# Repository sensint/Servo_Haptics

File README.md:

<div id="top"></div>

<!-- PROJECT SHIELDS -->
<!--
*** I'm using markdown "reference style" links for readability.
*** Reference links are enclosed in brackets [ ] instead of parentheses ( ).
*** See the bottom of this document for the declaration of the reference variables
*** for contributors-url, forks-url, etc. This is an optional, concise syntax you may use.
*** https://www.markdownguide.org/basic-syntax/#reference-style-links
-->
[![Contributors][contributors-shield]][contributors-url]
[![Forks][forks-shield]][forks-url]
[![Stargazers][stars-shield]][stars-url]
[![Issues][issues-shield]][issues-url]
[![MIT License][license-shield]][license-url]

<!-- PROJECT LOGO -->
<br />
<div align="center">

<h3 align="center">Haptic Servos - Motion Coupled Vibrations</h3>

  <p align="center">
    Self-Contained Vibrotactile Rendering System for Creating or Augmenting Material Experiences
    <br />
    <b>We'd love to get your feedback and get in touch with you: https://forms.gle/Dh4iDR7DPDSnXZQTA</b>
    <br />
    <br />
    <a href="https://github.com/sensint/Servo_Haptics/issues">Report Bug</a>
    ·
    <a href="https://github.com/sensint/Servo_Haptics/issues">Request Feature</a>
  </p>
</div>

## About The Project

![Banner images][banner-image]

<!--Add a summary of the project.-->

<p align="right">(<a href="#top">back to top</a>)</p>

### Built With

* [Teensyduino](https://www.pjrc.com/teensy/teensyduino.html)
* [PlatformIO](https://platformio.org/)

<p align="right">(<a href="#top">back to top</a>)</p>

## Getting Started

Download the code from the GitHub website or clone repo using your favorite git-client software or with the following command:

   ```sh
   git clone https://github.com/sensint/Servo_Haptics.git
   ```

### Firmware

We provide the firmware for two build systems - Teensyduino (based on Arduino IDE) and PlatformIO.

The firmware was tested with the following microcontrollers:

- Teensy 3.5
- Teensy 4.1

#### Teensyduino

The easiest way to get up and running with the firmware is Teensyduino.

##### Prerequisites

Download and install the [Teensyduino](https://www.pjrc.com/teensy/td_download.html) software for your operating system. All needed libraries are included in the basic installation.

##### Build and Upload

1. Open the `HapticServo.ino`
    1. navigate in your file manager (Win: Explorer, macOS: Finder) to the repository's folder `firmware/Teensyduino/MotionCoupledVibrations` and then double-click the `ino` file
    2. use the Teensyduino menu (`File -> Open`) or the keyboard shortcut (Win: `Ctrl+O`, macOS: `Cmd+O`) and navigate to the repository's folder `firmware/Teensyduino/MotionCoupledVibrations` and then select the `ino` file
2. connect the Teensy with your computer via USB
3. configure the Teensyduino
    1. select the correct board (Teensy version) from `Tools -> Board -> Teensydunio`
    2. select the correct serial port from `Tools -> Port`
4. click the upload button (arrow) in the Teensyduino IDE

<p align="right">(<a href="#top">back to top</a>)</p>

##### Control

The Haptic Servo is designed to be compatible with servo hardware and software. Using servo-commands you can fine-tune the tactile experience. You can find an example of how to do this in 'ServoControl.ino'

#### PlatformIO

##### Prerequisites

##### Build and Upload

<p align="right">(<a href="#top">back to top</a>)</p>

### Hardware

This project is based on the Teensy microcontroller and the [PT8211 Audio Kit](https://www.pjrc.com/store/pt8211_kit.html).

<p align="right">(<a href="#top">back to top</a>)</p>

## Usage

<!--Use this space to show useful examples of how a project can be used. Additional screenshots, code examples and demos work well in this space. You may also link to more resources.-->

<p align="right">(<a href="#top">back to top</a>)</p>

## Roadmap

See the [open issues](https://github.com/sensint/Servo_Haptics/issues) for a full list of proposed features (and known issues).

### Firmware

- [ ] ...

### Hardware

- [ ] ...

<p align="right">(<a href="#top">back to top</a>)</p>

## Contributing

Contributions are what make the open source community such an amazing place to learn, inspire, and create. Any contributions you make are **greatly appreciated**.

If you have a suggestion that would make this better, please fork the repo and create a pull request. You can also simply open an issue with the tag "enhancement".
Don't forget to give the project a star! Thanks again!

1. Fork the Project
2. Create your Feature Branch (`git checkout -b feature/AmazingFeature`)
3. Commit your Changes (`git commit -m 'Add some AmazingFeature'`)
4. Push to the Branch (`git push origin feature/AmazingFeature`)
5. Open a Pull Request

<p align="right">(<a href="#top">back to top</a>)</p>

## License

Distributed under the MIT License. See `LICENSE.txt` for more information.

<p align="right">(<a href="#top">back to top</a>)</p>

## Contact

Sensorimotor Interaction Group - [website](https://sensint.mpi-inf.mpg.de/) - [@sensintgroup](https://twitter.com/sensintgroup)

Project Link: [https://github.com/sensint/Servo_Haptics](https://github.com/sensint/Servo_Haptics)

<p align="right">(<a href="#top">back to top</a>)</p>

## Acknowledgments

* Othneil Drew for [Best-README-Template](https://github.com/othneildrew/Best-README-Template)

<p align="right">(<a href="#top">back to top</a>)</p>

<!-- MARKDOWN LINKS & IMAGES -->
<!-- https://www.markdownguide.org/basic-syntax/#reference-style-links -->
[contributors-shield]: https://img.shields.io/github/contributors/sensint/Servo_Haptics.svg?style=for-the-badge
[contributors-url]: https://github.com/sensint/Servo_Haptics/graphs/contributors
[forks-shield]: https://img.shields.io/github/forks/sensint/Servo_Haptics.svg?style=for-the-badge
[forks-url]: https://github.com/sensint/Servo_Haptics/network/members
[stars-shield]: https://img.shields.io/github/stars/sensint/Servo_Haptics.svg?style=for-the-badge
[stars-url]: https://github.com/sensint/Servo_Haptics/stargazers
[issues-shield]: https://img.shields.io/github/issues/sensint/Servo_Haptics.svg?style=for-the-badge
[issues-url]: https://github.com/sensint/Servo_Haptics/issues
[license-shield]: https://img.shields.io/github/license/sensint/Servo_Haptics.svg?style=for-the-badge
[license-url]: https://github.com/sensint/Servo_Haptics/blob/master/LICENSE
[banner-image]: assets/img/banner_temp.PNG

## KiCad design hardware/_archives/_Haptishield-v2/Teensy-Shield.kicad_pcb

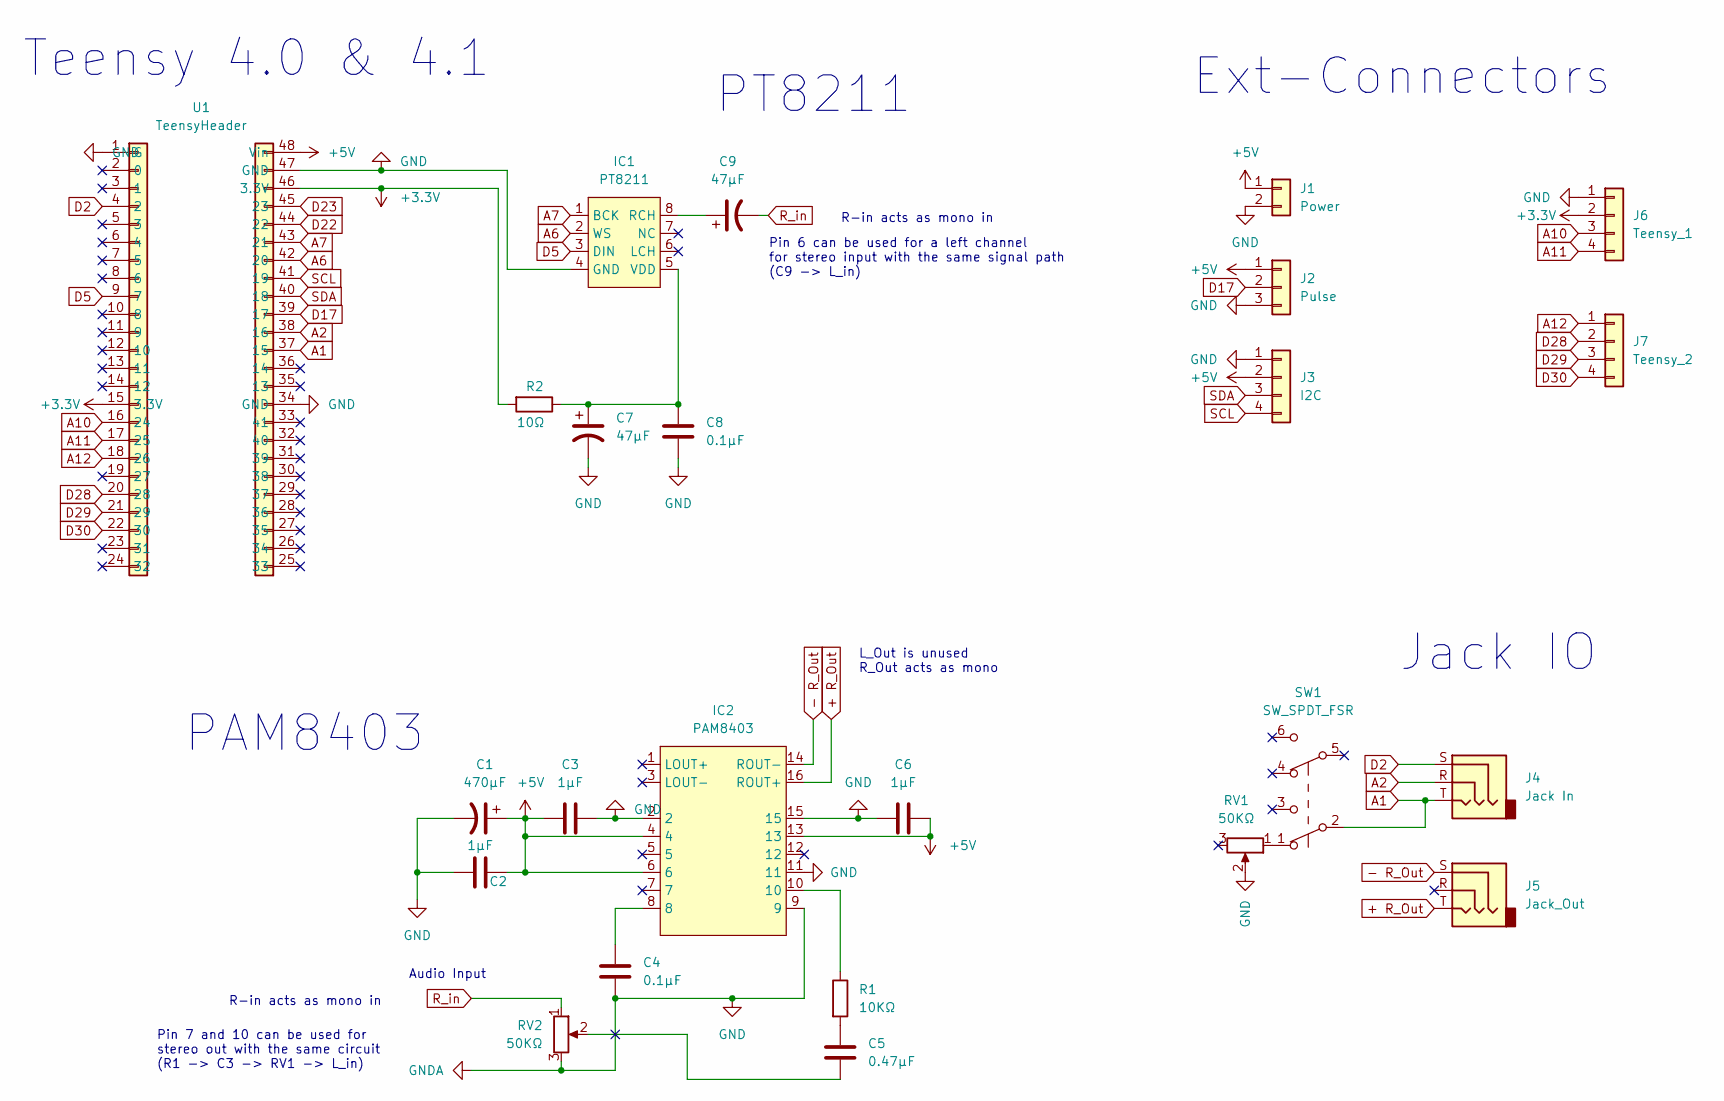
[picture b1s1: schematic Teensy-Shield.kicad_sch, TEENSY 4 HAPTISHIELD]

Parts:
C1: 470µF; CP_Radial_D5.0mm_P2.00mm
C2, C3, C6: 1µF; C_0805_2012Metric_Pad1.18x1.45mm_HandSolder
C4, C8: 0.1µF; C_0805_2012Metric_Pad1.18x1.45mm_HandSolder
C5: 0.47µF; C_0805_2012Metric_Pad1.18x1.45mm_HandSolder
C7, C9: 47µF; CP_Radial_D4.0mm_P1.50mm
IC1: PT8211; SOP-8_3.9x4.9mm_P1.27mm
IC2: PAM8403; SOIC-16_3.9x9.9mm_P1.27mm
J1: Power; PinHeader_1x02_P2.54mm_Vertical
J2: Pulse; PinHeader_1x03_P2.54mm_Vertical
J3: I2C; PinHeader_1x04_P2.54mm_Vertical
J4: Jack In; Jack_3.5mm_CUI_SJ1-3535NG_Horizontal_CircularHoles
J5: Jack_Out; Jack_3.5mm_CUI_SJ1-3535NG_Horizontal_CircularHoles
J6: Teensy_1; PinHeader_1x04_P2.54mm_Vertical
J7: Teensy_2; PinHeader_1x04_P2.54mm_Vertical
R1: 10KΩ; R_0805_2012Metric_Pad1.20x1.40mm_HandSolder
R2: 10Ω; R_0805_2012Metric_Pad1.20x1.40mm_HandSolder
RV1, RV2: 50KΩ; TRIM_3362P-1-503TLF
SW1: SW_SPDT_FSR; SW_CuK_JS202011CQN_DPDT_Straight
U1: TeensyHeader; Teensy41

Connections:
+3V3: J6.2, R2.2, U1.15 (3.3V), U1.46 (3.3V)
+5V: C1.1, C2.2, C3.1, C6.2, IC2.4, IC2.6, IC2.13, J1.1, J2.1, J3.2, U1.48 (Vin)
+ R_Out: IC2.16 (ROUT+), J5.T
- R_Out: IC2.14 (ROUT-), J5.S
A1: J4.T, SW1.2 (B), U1.37 (15)
A2: J4.R, U1.38 (16)
A6: IC1.2 (WS), U1.42 (20)
A7: IC1.1 (BCK), U1.43 (21)
A10: J6.3, U1.16 (24)
A11: J6.4, U1.17 (25)
A12: J7.1, U1.18 (26)
D2: J4.S, U1.4 (2)
D5: IC1.3 (DIN), U1.9 (7)
D17: J2.2, U1.39 (17)
D22: U1.44 (22)
D23: U1.45 (23)
D28: J7.2, U1.20 (28)
D29: J7.3, U1.21 (29)
D30: J7.4, U1.22 (30)
GND: C1.2, C2.1, C3.2, C4.2, C6.1, C7.2, C8.2, IC1.4 (GND), IC2.2, IC2.9, IC2.11, IC2.15, J1.2, J2.3, J3.1, J6.1, RV1.2, RV2.3, U1.1 (G), U1.34 (GND), U1.47 (GND)
unnamed: C4.1, IC2.8
unnamed: C5.1, R1.2
unnamed: C5.2, RV2.2
unnamed: C7.1, C8.1, IC1.5 (VDD), R2.1
unnamed: C9.1, IC1.8 (RCH)
unnamed: IC2.10, R1.1
unnamed: RV1.1, SW1.1 (A)
R_in: C9.2, RV2.1
SCL: J3.4, U1.41 (19)
SDA: J3.3, U1.40 (18)

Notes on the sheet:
Jack IO
R-in acts as mono in
Pin 7 and 10 can be used for stereo out with the same circuit (R1 -> C3 -> RV1 -> L_in)
Audio Input
PAM8403
PT8211
Pin 6 can be used for a left channel for stereo input with the same signal path (C9 -> L_in)
Ext-Connectors
Teensy 4.0 & 4.1
L_Out is unused R_Out acts as mono

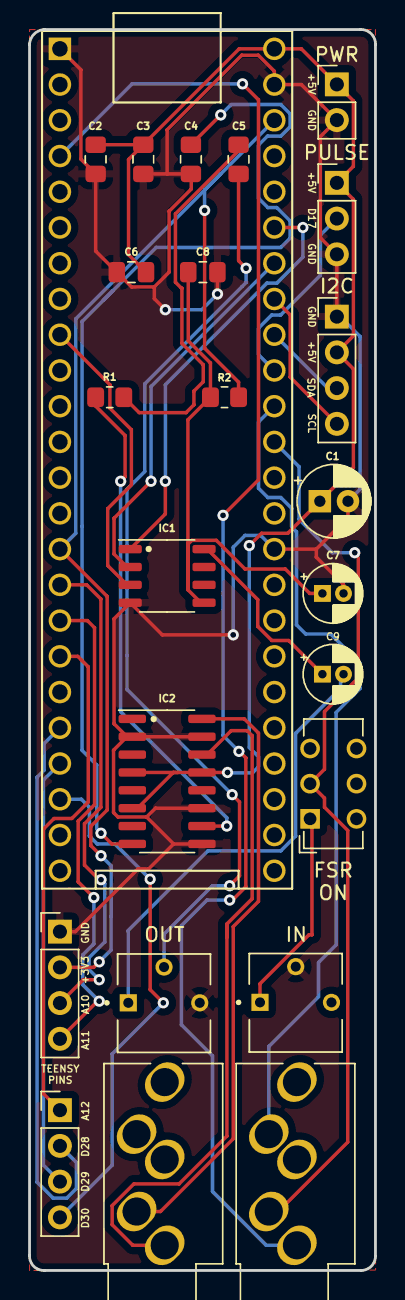
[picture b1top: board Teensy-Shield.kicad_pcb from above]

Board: 2 copper layers, 24.6 x 88.2 mm, 24 parts (0 on the bottom side), 28 nets.

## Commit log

2022-03-21 docs: :tada: add basic project setup and introduction
2022-03-21 fix: :memo: refactor links
2022-03-21 docs: :memo: add twitter handle
2022-03-22 feat: :sparkles: original code
    This is the original code used for the first experiments.
2022-03-22 feat: :sparkles: port for PlatformIO
    This commit adds the project setup for PlatformIO based on the Teensyduino code.
2022-03-22 docs: :memo: update contact information
2022-03-24 feat: :sparkles: benchmark code execution
2022-03-24 refactor: :recycle: clean code
2022-03-25 fix: :bug: number of bins needs to be one less
    We use the number of bins to retrieve the current bin number. Since the first bin has the id 0 we need to reduce the value by one.
2022-03-25 refactor: :construction: finished benchmarking the electrical latency
    We measured the electrical latency of the system, i.e. the time from triggering a sensor to the start of the audio signal. This is measured at the output of the DAC.
2022-03-28 fix: :bug: reset waveform at pulse start
    To start a new pulse we need to first set the correct amplitude and then restart the waveform.
2022-03-28 fix:
2022-03-28 fix: :bug: force inlining of functions
2022-03-28 feat: :sparkles: add arbitrary waveform for benchmarking
2022-03-28 feat: :construction: use random delays between iterations
2022-03-28 feat: :rocket: finish benchmarks
2022-03-28 refactor: :recycle: move code for arbitrary wave to benchmark
2022-03-29 docs: :memo: benchmark procedure
2022-03-29 feat: :sparkles: read servo signals
    We provide a easy to use interface based on the Servo library to simplify the design process of motion coupled vibration. Therefore, we provide predefined lookup tables of signal parameters one could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
2022-03-30 fix: :bug: initialize servo pin
2022-03-30 refactor: :construction: change servo pin
2022-03-30 feat: :sparkles: LUT generator
    This provides a Processing sketch to create LUTs for parametrization curves.
2022-03-30 refactor: :card_file_box: add LUT from generator
2022-03-31 feat: :sparkles: add three types of LUT generation functions
2022-03-31 refactor: :recycle: remove redundancies
2022-03-31 chore: :truck: rename software
2022-03-31 fix: :bug: slowed down reading a servo with interrupts and timer
2022-03-31 feat: :sparkles: demo of a Haptic Servo
2022-03-31 build: :construction_worker: configure for development build
2022-03-31 feat: :rocket: port firmware to Teensyduino
2022-07-05 CAD resources to hardware
2022-08-17 feat(firmware): :rocket: finish version 1.0.0 for the workshop
2022-08-17 feat(firmware): :sparkles: prepare release for workshop
2022-08-17 feat(LUT generator): :iphone: change color scheme
2022-09-22 HS Haptishield v2 files and schematics added
2022-11-15 Reason for hardware fix- Pin 2 Low
    Creating a virtual ground.
2023-01-27 update title
2023-11-27 Add Haptic Servo V3 CAD and BOM
2024-01-28 add simple grain-based compliance illusion
